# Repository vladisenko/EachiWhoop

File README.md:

# EachiWhoop v2

Changes compared to the v1:
- Upgrade CPU to STM32F303CCT6
- Add support AFHDS A2 protocol with telemetry (tested with FlySky FS-i6 transmitter)
- Add pads for the UART
- Board can operate with 2S battery (not tested yet)

# EachiWhoop

Micro size flight controller board for Eachine E010 frame.

Specifications:
- Processor: STM32F103CB
- Gyro: MPU6500
- Receiver: Flysky AFHDS
- Weight: 1.44 grams
- Voltage: 1S Lipo battery input
- Firmware: patched Betaflight

PCB with "2oz 0.8mm" option from [OSH Park](https://oshpark.com/shared_projects/v77xm6IP).

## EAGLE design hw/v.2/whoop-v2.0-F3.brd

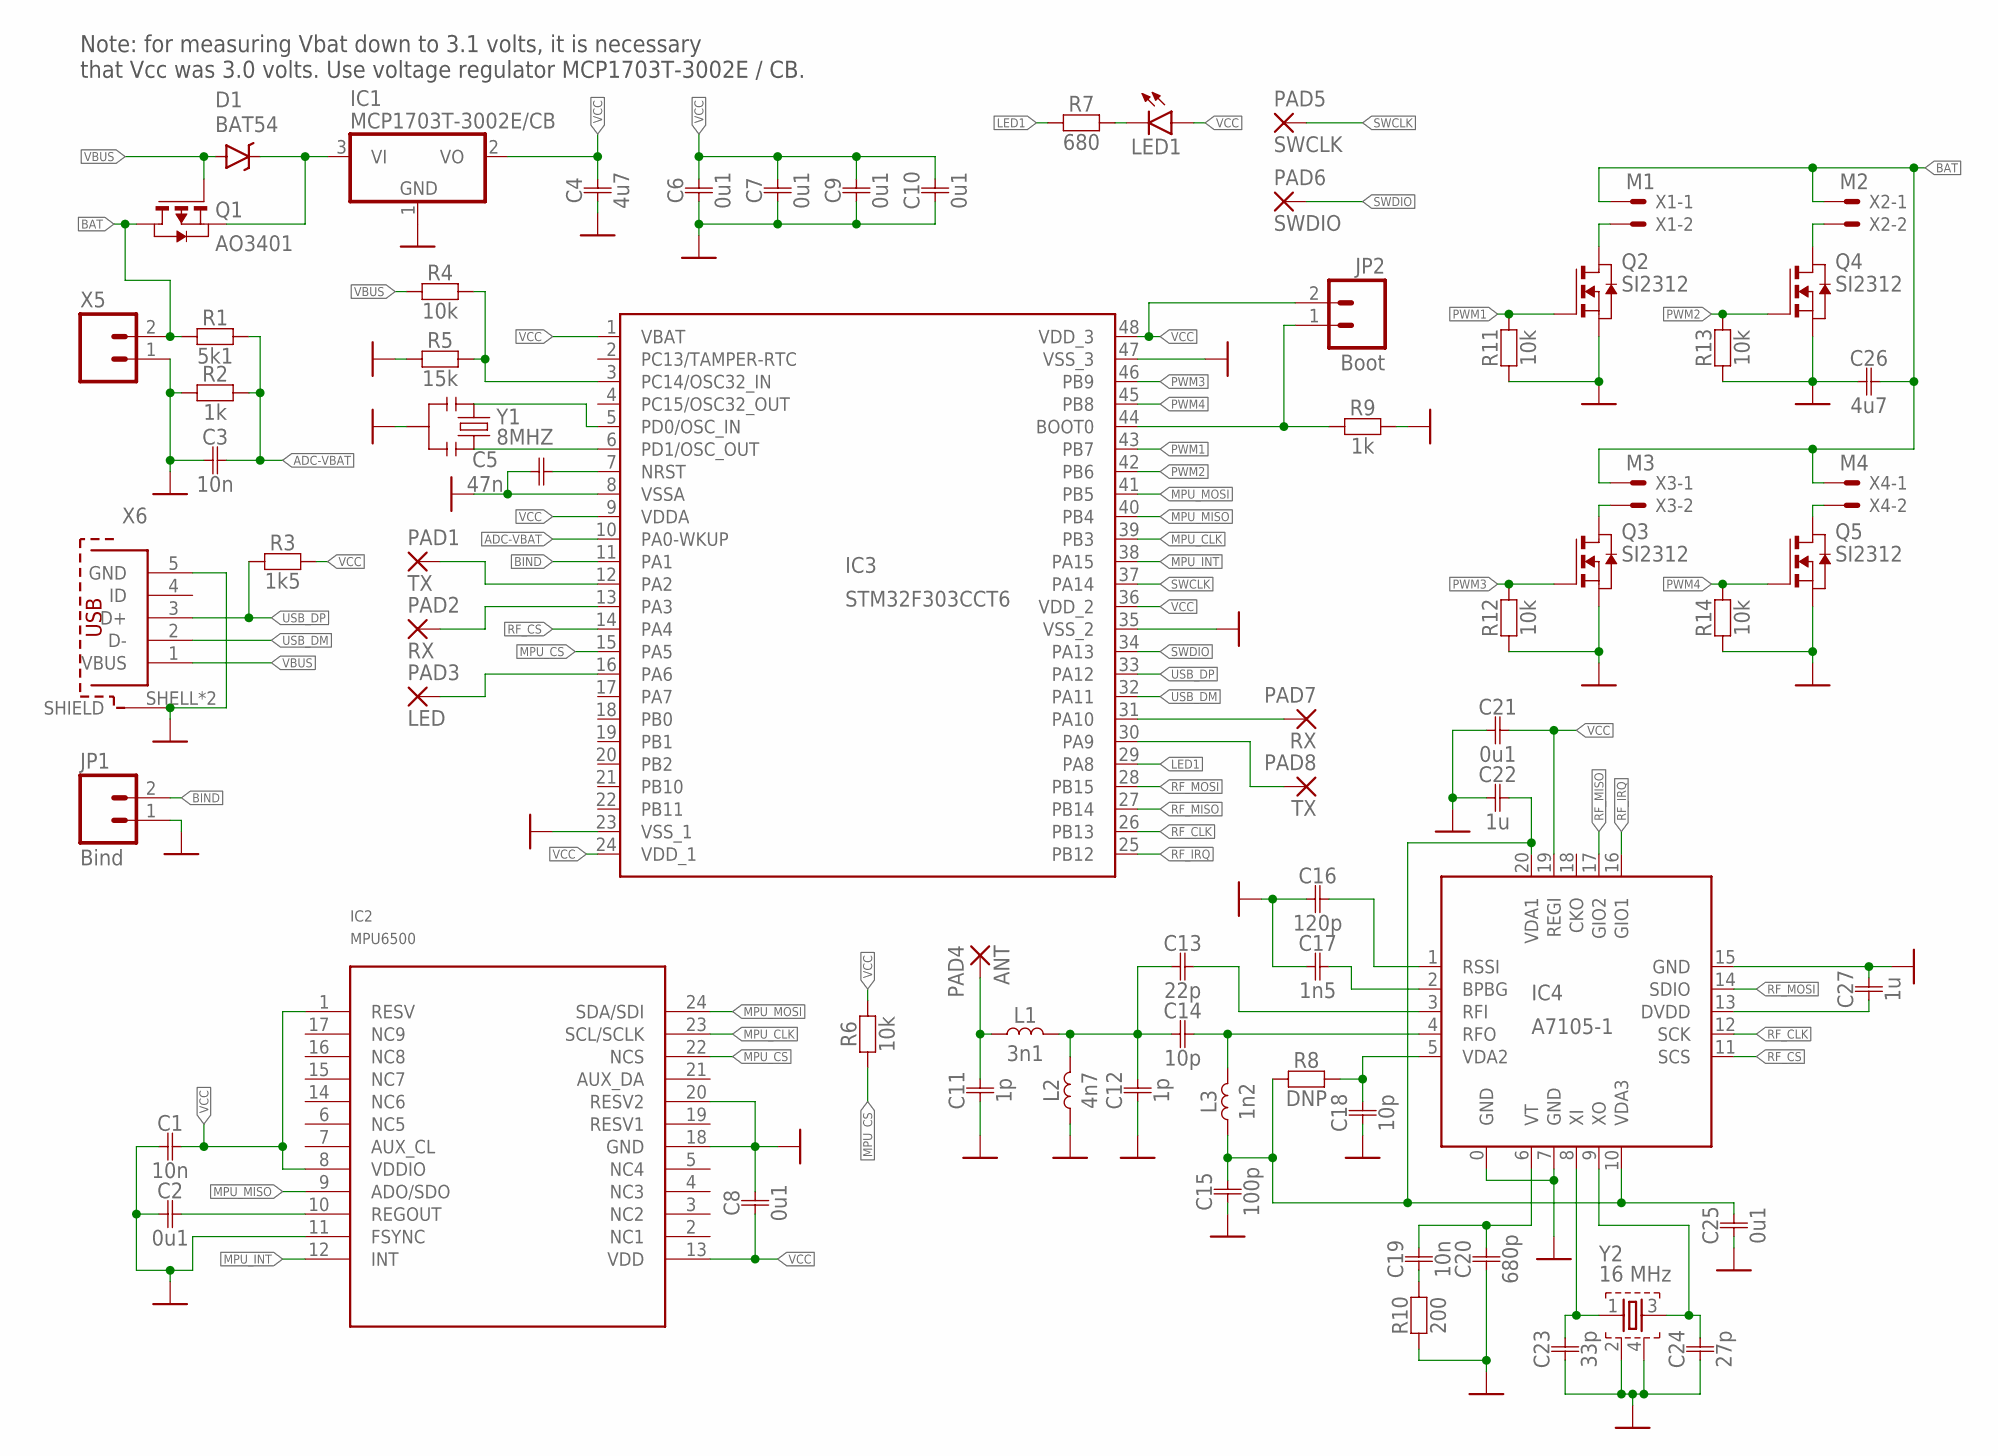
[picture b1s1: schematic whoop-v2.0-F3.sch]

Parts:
C1, C3, C19: 10n; 0402
C2, C6, C7, C8, C9, C10, C21, C25: 0u1; 0402
C4, C26: 4u7; 0805
C5: 47n; 0402
C11, C12: 1p; 0402
C13: 22p; 0402
C14, C18: 10p; 0402
C15: 100p; 0402
C16: 120p; 0402
C17: 1n5; 0402
C20: 680p; 0402
C22, C27: 1u; 0402
C23: 33p; 0402
C24: 27p; 0402
D1: BAT54; SOD-323
IC1: MCP1703T-3002E/CB; SOT23
IC2: MPU6500; LEAD-QFN24
IC3: STM32F303CCT6; LQFP48
IC4: A7105-1; QFN20-1
JP1: Bind; 1X02_1.27MM
JP2: Boot; 1X02_1.27MM
L1: 3n1; 0402
L2: 4n7; 0402
L3: 1n2; 0402
LED1: LED-RED0603; LED-0603
PAD1: TX; SMD_R0,635
PAD2, PAD7: RX; 1/0,6
PAD3: LED; 1/0,6
PAD4: ANT; 1/0,6
PAD5: SWCLK; SMD_R0,635
PAD6: SWDIO; SMD_R0,635
PAD8: TX; 1/0,6
Q1: AO3401; SOT-23
Q2, Q3, Q4, Q5: SI2312; SOT-23
R1: 5k1; 0402
R2, R9: 1k; 0402
R3: 1k5; 0402
R4, R6, R11, R12, R13, R14: 10k; 0402
R5: 15k; 0402
R7: 680; 0402
R8: DNP; 0402
R10: 200; 0402
X1: M1; 53047-02
X2: M2; 53047-02
X3: M3; 53047-02
X4: M4; 53047-02
X5: M022MM; 1X02_2MM
X6: 614105150721
Y1: 8MHZ; RESONATOR-SMD
Y2: 16 MHz; FA-20H

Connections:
ADC-VBAT: C3.P$2, IC3.10 (PA0-WKUP), R1.P$1, R2.P$1
BAT: C26.P$2, Q1.1 (D), R1.P$2, X1.1, X2.1, X3.1, X4.1, X5.2
BIND: IC3.11 (PA1), JP1.2
GND: C1.P$1, C2.P$1, C3.P$1, C4.P$1, C5.P$1, C6.P$1, C7.P$1, C8.P$2, C9.P$1, C10.P$1, C11.P$1, C12.P$1, C15.P$1, C16.P$1, C17.P$1, C18.P$1, C20.P$1, C21.P$1, C22.P$1, C23.P$1, C24.P$1, C25.P$1, C26.P$1, C27.P$2, IC1.1 (GND), IC2.11 (FSYNC), IC2.18 (GND), IC2.20 (RESV2), IC3.8 (VSSA), IC3.23 (VSS_1), IC3.35 (VSS_2), IC3.47 (VSS_3), IC4.0 (GND), IC4.7 (GND), IC4.15 (GND), JP1.1, L2.P$1, Q2.2 (S), Q3.2 (S), Q4.2 (S), Q5.2 (S), R2.P$2, R5.P$2, R9.P$2, R10.P$1, R11.P$1, R12.P$1, R13.P$1, R14.P$1, X5.1, X6.5 (GND), X6.SHELL (SHIELD), X6.SHELL1 (SHIELD), Y1.2, Y2.2, Y2.4
LED1: IC3.29 (PA8), R7.P$1
M1+: Q2.1 (D), X1.2
M2+: Q4.1 (D), X2.2
M3+: Q3.1 (D), X3.2
M4+: Q5.1 (D), X4.2
MPU_CLK: IC2.23 (SCL/SCLK), IC3.39 (PB3)
MPU_CS: IC2.22 (NCS), IC3.15 (PA5), R6.P$1
MPU_INT: IC2.12 (INT), IC3.38 (PA15)
MPU_MISO: IC2.9 (ADO/SDO), IC3.40 (PB4)
MPU_MOSI: IC2.24 (SDA/SDI), IC3.41 (PB5)
unnamed: C13.P$2, IC4.3 (RFI)
unnamed: C12.P$2, C13.P$1, C14.P$1, L1.P$2, L2.P$2
unnamed: C2.P$2, IC2.10 (REGOUT)
unnamed: C14.P$2, IC4.4 (RFO), L3.P$1
unnamed: C23.P$2, IC4.8 (XI), Y2.1
unnamed: C24.P$2, IC4.9 (XO), Y2.3
unnamed: C17.P$2, IC4.2 (BPBG)
unnamed: C16.P$2, IC4.1 (RSSI)
unnamed: C19.P$2, C20.P$2, IC4.6 (VT)
unnamed: C27.P$1, IC4.13 (DVDD)
unnamed: C19.P$1, R10.P$2
unnamed: C15.P$2, C22.P$2, C25.P$2, IC4.10 (VDA3), IC4.20 (VDA1), L3.P$2, R8.P$1
unnamed: IC3.6 (PD1/OSC_OUT), Y1.3
unnamed: C18.P$2, IC4.5 (VDA2), R8.P$2
unnamed: LED1.C, R7.P$2
unnamed: IC3.12 (PA2), PAD1.1
unnamed: IC3.3 (PC14/OSC32_IN), R4.P$2, R5.P$1
unnamed: IC3.13 (PA3), PAD2.1
unnamed: IC3.44 (BOOT0), JP2.1, R9.P$1
unnamed: C11.P$2, L1.P$1, PAD4.1
unnamed: IC3.31 (PA10), PAD7.1
unnamed: IC3.16 (PA6), PAD3.1
unnamed: IC3.30 (PA9), PAD8.1
unnamed: IC3.5 (PD0/OSC_IN), Y1.1
unnamed: D1.C, IC1.3 (VI), Q1.2 (S)
unnamed: C5.P$2, IC3.7 (NRST)
PWM1: IC3.43 (PB7), Q2.3 (G), R11.P$2
PWM2: IC3.42 (PB6), Q4.3 (G), R13.P$2
PWM3: IC3.46 (PB9), Q3.3 (G), R12.P$2
PWM4: IC3.45 (PB8), Q5.3 (G), R14.P$2
RF_CLK: IC3.26 (PB13), IC4.12 (SCK)
RF_CS: IC3.14 (PA4), IC4.11 (SCS)
RF_IRQ: IC3.25 (PB12), IC4.16 (GIO1)
RF_MISO: IC3.27 (PB14), IC4.17 (GIO2)
RF_MOSI: IC3.28 (PB15), IC4.14 (SDIO)
SWCLK: IC3.37 (PA14), PAD5.1
SWDIO: IC3.34 (PA13), PAD6.1
USB_DM: IC3.32 (PA11), X6.2 (D-)
USB_DP: IC3.33 (PA12), R3.P$2, X6.3 (D+)
VBUS: D1.A, Q1.3 (G), R4.P$1, X6.1 (VBUS)
VCC: C1.P$2, C4.P$2, C6.P$2, C7.P$2, C8.P$1, C9.P$2, C10.P$2, C21.P$2, IC1.2 (VO), IC2.1 (RESV), IC2.8 (VDDIO), IC2.13 (VDD), IC3.1 (VBAT), IC3.9 (VDDA), IC3.24 (VDD_1), IC3.36 (VDD_2), IC3.48 (VDD_3), IC4.19 (REGI), JP2.2, LED1.A, R3.P$1, R6.P$2

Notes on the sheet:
Note: for measuring Vbat down to 3.1 volts, it is necessary that Vcc was 3.0 volts. Use voltage regulator MCP1703T-3002E / CB.

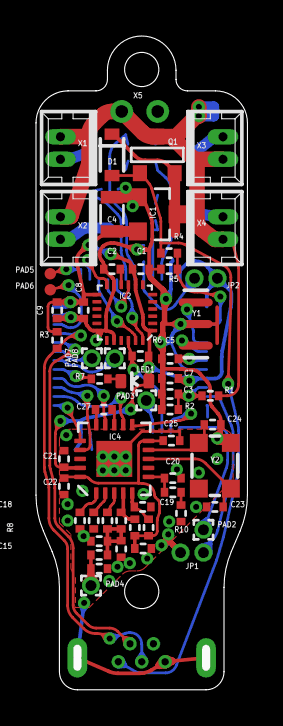
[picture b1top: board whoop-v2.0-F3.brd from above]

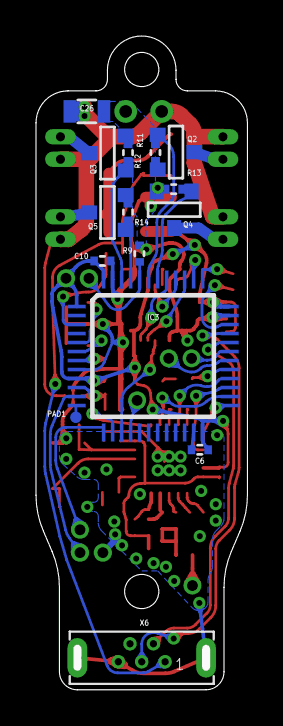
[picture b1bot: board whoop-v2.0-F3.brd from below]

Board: 2 copper layers, 11.3 x 35.9 mm, 73 parts (15 on the bottom side), 55 nets.

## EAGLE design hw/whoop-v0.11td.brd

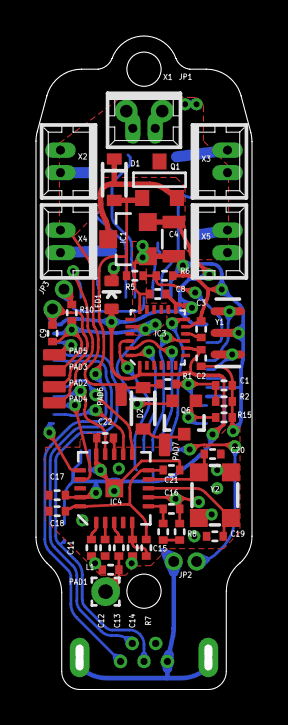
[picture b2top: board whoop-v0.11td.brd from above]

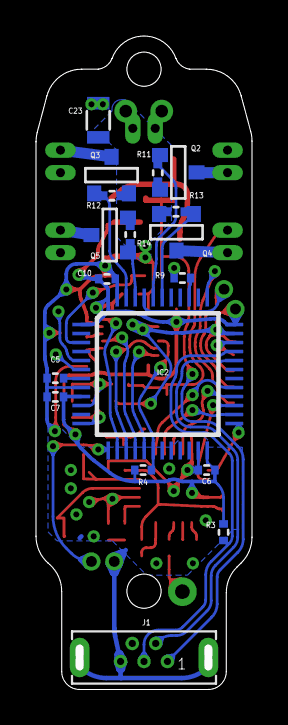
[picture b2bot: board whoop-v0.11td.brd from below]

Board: 2 copper layers, 11.6 x 35.9 mm, 70 parts (18 on the bottom side), 50 nets.

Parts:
C1, C2, C15: 10n; 0402
C3, C6, C7, C8, C9, C10, C14, C17, C18, C21, C22: 0u1; 0402
C4, C23: 4u7; 0805
C5: 47n; 0402
C11: 120p; 0402
C12: 1n5; 0402
C13: 3p9; 0402
C16: 560p; 0402
C19, C20: 33p; 0402
D1, D2: BAT54; SOD-323
IC1: MCP1703CB; SOT23
IC2: STM32F103CBT6; LQFP48
IC3: MPU6500; LEAD-QFN24
IC4: A7105; QFN20
J1: 614105150721
JP1: 1X02_2MM
JP2: Bind; 1X02_1.27MM
JP3: Boot; 1X02_1.27MM
L1: 0402
LED1: LED-0603
PAD1: ANT; 1,6/0,8
PAD2: VCC; SMD1,27-2,54
PAD3: GND; SMD1,27-2,54
PAD4: SWCLK; SMD1,27-2,54
PAD5: SWDIO; SMD1,27-2,54
PAD6: BUZ+; SMD1,27-2,54
PAD7: BUZ-; SMD1,27-2,54
Q1: AO3401; SOT-23
Q2, Q3, Q4, Q5: SI2312; SOT-23
Q6: 2N7002; SOT323
R1, R2, R10: 1k; 0402
R3: 1k5; 0402
R4, R5, R11, R12, R13, R14, R15: 10k; 0402
R6: 15k; 0402
R7: DNP; 0402
R8: 200; 0402
R9: 680; 0402
X1: BAT; 53047-02
X2: M4; 53047-02
X3: M2; 53047-02
X4: M3; 53047-02
X5: M1; 53047-02
Y1: 8MHZ; RESONATOR-SMD
Y2: 16 MHz; FA-20H

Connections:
ADC-VBAT: C1.P$2, IC2.10, R1.P$1, R2.P$1
BAT: C23.P$2, D2.C, JP1.2, PAD6.1, Q1.1, R1.P$2, X1.1, X2.1, X3.1, X4.1, X5.1
BEEP: IC2.12, Q6.1, R15.P$2
BIND: IC2.13, JP2.2
GND: C1.P$1, C2.P$1, C3.P$1, C4.P$1, C5.P$1, C6.P$1, C7.P$1, C8.P$2, C9.P$1, C10.P$1, C11.P$1, C12.P$1, C14.P$1, C16.P$1, C17.P$1, C18.P$1, C19.P$1, C20.P$1, C21.P$1, C22.P$2, C23.P$1, IC1.1, IC2.8, IC2.23, IC2.35, IC2.47, IC3.11, IC3.18, IC3.20, IC4.0, IC4.7, IC4.15, J1.5, J1.SHELL, J1.SHELL1, JP1.1, JP2.1, L1.P$1, PAD3.1, Q2.2, Q3.2, Q4.2, Q5.2, Q6.2, R2.P$2, R6.P$2, R8.P$1, R10.P$2, R11.P$1, R12.P$1, R13.P$1, R14.P$1, R15.P$1, X1.2, Y1.2, Y2.2, Y2.4
M1+: Q2.1, X2.2
M2+: Q4.1, X4.2
M3+: Q3.1, X3.2
M4+: Q5.1, X5.2
MPU_CLK: IC2.15, IC3.23
MPU_CS: IC2.18, IC3.22, R4.P$1
MPU_INT: IC2.14, IC3.12
MPU_MISO: IC2.16, IC3.9
MPU_MOSI: IC2.17, IC3.24
unnamed: C13.P$2, IC4.3
unnamed: D2.A, PAD7.1, Q6.3
unnamed: C3.P$2, IC3.10
unnamed: C13.P$1, L1.P$2, PAD1.1
unnamed: C19.P$2, IC4.8, Y2.1
unnamed: C20.P$2, IC4.9, Y2.3
unnamed: C12.P$2, IC4.2
unnamed: C11.P$2, IC4.1
unnamed: C15.P$2, C16.P$2, IC4.6
unnamed: C22.P$1, IC4.13
unnamed: C15.P$1, R8.P$2
unnamed: C18.P$2, C21.P$2, IC4.10, IC4.20, R7.P$1
unnamed: IC2.6, Y1.3
unnamed: C14.P$2, IC4.5, R7.P$2
unnamed: LED1.C, R9.P$2
unnamed: IC2.39, R9.P$1
unnamed: IC2.3, R5.P$2, R6.P$1
unnamed: IC2.44, JP3.1, R10.P$1
unnamed: IC2.5, Y1.1
unnamed: D1.C, IC1.3, Q1.2
unnamed: C5.P$2, IC2.7
PWM1: IC2.45, Q5.3, R14.P$2
PWM2: IC2.46, Q3.3, R12.P$2
PWM3: IC2.42, Q4.3, R13.P$2
PWM4: IC2.43, Q2.3, R11.P$2
RF_CLK: IC2.26, IC4.12
RF_CS: IC2.29, IC4.11
RF_IRQ: IC2.25, IC4.16
RF_MISO: IC2.27, IC4.17
RF_MOSI: IC2.28, IC4.14
SWCLK: IC2.37, PAD4.1
SWDIO: IC2.34, PAD5.1
USB_DM: IC2.32, J1.2
USB_DP: IC2.33, J1.3, R3.P$2
VBUS: D1.A, J1.1, Q1.3, R5.P$1
VCC: C2.P$2, C4.P$2, C6.P$2, C7.P$2, C8.P$1, C9.P$2, C10.P$2, C17.P$2, IC1.2, IC2.1, IC2.9, IC2.24, IC2.36, IC2.48, IC3.1, IC3.8, IC3.13, IC4.19, JP3.2, LED1.A, PAD2.1, R3.P$1, R4.P$2

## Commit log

2017-02-19 :neckbeard: Added .gitattributes
2017-02-19 first release
2017-02-20 hw update
2017-02-20 add photo
2017-02-20 edit readme
2017-03-06 add v2 of hardware
2017-04-06 edit some values
2017-04-06 add firmware for v.2
2017-04-09 update to new version
2017-04-10 code cleanup
2017-09-06 update to v3.2.0-RC4

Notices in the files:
parts and their libraries:
SparkFun-DiscreteSemi: Licensing: Creative Commons ShareAlike 4.0 International - https://creativecommons.org/licenses/by-sa/4.0
